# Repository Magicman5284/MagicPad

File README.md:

Welcome to the MagicPad!

This is my attempt to create a smarthome control device. 
Recently I've made a couple smart devices controlled by esp32s, so I wanted to make a device that could control them. 
The two devices it's set up to control right now are my coffee maker and my alarm clock. 
Because these are both custom projects, I don't see the MagicPad's current firmware being useful to anyone else, but that hardware can be used to control any device that can be controlled over wifi!
Because of how versatile the hardware is, it has plenty of room for future expansion such as adding games!

Assembly:
- Pretty self-explanatory for the most part, just solder the components where they are in the 3d model. 
- The one tricky part is the battery.
- To connect the battery, solder the negative wire from the battery holder into the hole in the board to the right of the buttons. 
- After this, directly solder the positive wire to the positive pin on the battery connector of the ESP32. 
- To determine which one a the positive pin, a multimeter on beeper mode can be used between both pins and ground. if it beeps, that pin is negative. 
- You also might need some additional dupont connectors to raise the screen up so it's not swallowed by the case

  Useage:
- I think the UI is pretty self-explanatory and probably no one else is ever gonna use it, so I'm not gonna bother explaining it. 
- The switch in the bottom right is a power switch
- I know this is bad design, but the device needs to be powered ON in order for it to charge. 
- Bottom left button is a back button and top right is a home button. 
- You need to input wifi and IP information in the sketch before you upload it

BOM:
| Item                                                                                                                 | Qty | Supplier            | Cost/item | Total Cost | link                                                                                                                                                                                                                                                                                                                                                                                                                                                                                                                                                                                                                                                                                                                                                                                  |
|----------------------------------------------------------------------------------------------------------------------|-----|---------------------|-----------|------------|---------------------------------------------------------------------------------------------------------------------------------------------------------------------------------------------------------------------------------------------------------------------------------------------------------------------------------------------------------------------------------------------------------------------------------------------------------------------------------------------------------------------------------------------------------------------------------------------------------------------------------------------------------------------------------------------------------------------------------------------------------------------------------------|
| 2.4 in tft screen                                                                                                    | 1   | Aliexpress          | $3.85     | $3.85      | https://www.aliexpress.us/item/3256808368541153.html?spm=a2g0o.productlist.main.3.149d3f62npL2uj&algo_pvid=60c42d40-368a-4445-8d6c-448ea058a9be&algo_exp_id=60c42d40-368a-4445-8d6c-448ea058a9be-2&pdp_ext_f=%7B%22order%22%3A%222129%22%2C%22eval%22%3A%221%22%2C%22fromPage%22%3A%22search%22%7D&pdp_npi=6%40dis%21USD%214.51%213.85%21%21%214.51%213.85%21%402103117b17940812731455001e0f3a%2112000056541994976%21sea%21US%212783459362%21X%211%210%21n_tag%3A-29919%3Bd%3Abaf43391%3Bm03_new_user%3A-29895%3BpisId%3A5000000220844609&curPageLogUid=2lMKeavTadMR&utparam-url=scene%3Asearch%7Cquery_from%3A%7Cx_object_id%3A1005008554855905%7C_p_origin_prod%3A                                                                                                                  |
| ESP32-S Development Board 2.4G Wifi Module with Battery Interface Original Ai ESP32-S for DIY IoT CH340X IP5306 Type | 1   | Aliexpress          | $6.32     | $6.32      | https://www.aliexpress.us/item/3256808312600406.html?spm=a2g0o.cart.0.0.77df38daxh0mED&mp=1&pdp_npi=6%40dis%21USD%21USD+6.97%21USD+6.32%21%21USD+6.19%21%21%21%402101e80f17940814752793414e0d72%2112000045422070092%21ct%21US%212783459362%21%211%210%21&_gl=1*10hfm7j*_gcl_aw*R0NMLjE3OTM4MjY5OTQuQ2p3S0NBaUF6S3ZYQmhCQUVpd0FCTGw5QXJHaTJzQVl2NlFzaE5UUmw4dkxZT2tkWXU5MnhxZTFSRC13d19LSW5sd281dHJEaFExc014b0NuWGNRQXZEX0J3RQ..*_gcl_dc*R0NMLjE3OTI4OTA3OTYuQ2owS0NRandydkhXQmhES0FSSXNBQm1wN2gzWWRremlEblp6RmlpOFV6R3JzMWxXNWw0WDhubmFnbzd2bUhkMEdZZW5pTHQ3bzlqbklQSWFBalZoRUFMd193Y0I.*_gcl_au*MzM2NDgyMzA5LjE3ODk1ODM4Mzc.*_ga*ODUyMzUwNzk1LjE3OTMxMzg2Mjc.*_ga_VED1YSGNC7*czE3OTQwODEyNjEkbzE4JGcxJHQxNzk0MDgxNDczJGo2JGwwJGgw&gatewayAdapt=glo2usa                               |
| 18650 battery holder                                                                                                 | 1   | Aliexpress          | $0.99     | $0.99      | https://www.aliexpress.us/item/2251832638846318.html?spm=a2g0o.cart.0.0.235338daUdxJp9&mp=1&pdp_npi=6%40dis%21USD%21USD+1.13%21USD+0.99%21%21USD+0.98%21%21%21%40210327ef17940815433297406e0d19%2164904655701%21ct%21US%212783459362%21%211%210%21&gatewayAdapt=glo2usa                                                                                                                                                                                                                                                                                                                                                                                                                                                                                                               |
| 18650 battery                                                                                                        | 1   | 18650 battery store | $4.99     | $4.99      | https://www.18650batterystore.com/products/samsung-25r-18650?variant=37119890063511&country=US&currency=USD&utm_medium=product_sync&utm_source=google&utm_content=sag_organic&utm_campaign=sag_organic&utm_campaign=23969421789&utm_source=g_c&utm_medium=cpc&utm_content=814166832664&utm_term=_&adgroupid=200718758591&gad_source=4&gad_campaignid=23969421789&gbraid=0AAAAADl22IP-T0yCTHMd2LJW7-kmlS5L0&gclid=CjwKCAiAtbvXBhB_EiwAjwv9Ji52yHABlerJVfGG0AsgF0rU-j0VmBES08tR3X1S4KTzMIlJhsAiJhoC3NIQAvD_BwE                                                                                                                                                                                                                                                                          |
| minitoggle switch 3 prongs                                                                                           | 1   | Aliexpress          | $3.82     | $3.82      | https://www.aliexpress.us/item/3256808118023831.html?spm=a2g0o.productlist.main.4.339f31cfuvqRyR&aem_p4p_detail=202611071200442267456020120960004589159&algo_pvid=ffc93556-7054-4d00-a989-105471204cdd&algo_exp_id=ffc93556-7054-4d00-a989-105471204cdd-3&pdp_ext_f=%7B%22order%22%3A%223770%22%2C%22eval%22%3A%221%22%2C%22fromPage%22%3A%22search%22%7D&pdp_npi=6%40dis%21USD%214.54%213.82%21%21%2130.10%2125.31%21%4021030cd817940816442355963e0f71%2112000044555585169%21sea%21US%212783459362%21X%211%210%21n_tag%3A-29919%3Bd%3Abaf43391%3Bm03_new_user%3A-29895%3BpisId%3A5000000220844609&curPageLogUid=bxfWoncg7wrM&utparam-url=scene%3Asearch%7Cquery_from%3A%7Cx_object_id%3A1005008304338583%7C_p_origin_prod%3A&search_p4p_id=202611071200442267456020120960004589159_1 |
| EC11 rotary encoder with push button                                                                                 | 1   | Aliexpress          | $1.37     | $1.37      | https://www.aliexpress.us/item/3256807457768762.html?spm=a2g0o.productlist.main.3.5e1068b6ZSGLHV&algo_pvid=103bbf53-d7ff-41ed-948a-e11e77e458db&algo_exp_id=103bbf53-d7ff-41ed-948a-e11e77e458db-2&pdp_ext_f=%7B%22order%22%3A%224956%22%2C%22eval%22%3A%221%22%2C%22fromPage%22%3A%22search%22%7D&pdp_npi=6%40dis%21USD%211.52%211.32%21%21%211.52%211.32%21%4021030f4a17940817013391423e0ff3%2112000041630839409%21sea%21US%212783459362%21X%211%210%21n_tag%3A-29919%3Bd%3Abaf43391%3Bm03_new_user%3A-29895%3BpisId%3A5000000220844609&curPageLogUid=uPza42i6Mwl9&utparam-url=scene%3Asearch%7Cquery_from%3A%7Cx_object_id%3A1005007644083514%7C_p_origin_prod%3A                                                                                                                  |
| 10k resistor                                                                                                         | 1   | Aliexpress          | $1.53     | $1.53      | https://www.aliexpress.us/item/3256809143779506.html?spm=a2g0o.productlist.main.3.5a782a0a1rcJxt&algo_pvid=45ee8b2b-bcd2-4eb7-80b8-ee1bf72b4ad2&algo_exp_id=45ee8b2b-bcd2-4eb7-80b8-ee1bf72b4ad2-2&pdp_ext_f=%7B%22order%22%3A%229099%22%2C%22eval%22%3A%221%22%2C%22fromPage%22%3A%22search%22%7D&pdp_npi=6%40dis%21USD%211.81%211.53%21%21%2111.99%2110.12%21%402101e80f17940817994392860e1068%2112000048778024089%21sea%21US%212783459362%21X%211%210%21n_tag%3A-29919%3Bd%3Abaf43391%3Bm03_new_user%3A-29895%3BpisId%3A5000000220405735&curPageLogUid=K5N1yOKL6CDi&utparam-url=scene%3Asearch%7Cquery_from%3A%7Cx_object_id%3A1005009330094258%7C_p_origin_prod%3A                                                                                                                |
| 1x10 dupont connectors                                                                                               | 1   | Aliexpress          | $2.83     | $2.83      | https://www.aliexpress.us/item/3256811876826434.html?spm=a2g0o.cart.0.0.568d38danzfLHR&mp=1&pdp_npi=6%40dis%21USD%21USD+2.85%21USD+2.37%21%21USD+2.37%21%21%21%402101e80f17940820156671223e0d72%2112000057466932458%21ct%21US%212783459362%21%211%210%21&_gl=1*ruz3ms*_gcl_aw*R0NMLjE3OTM4MjY5OTQuQ2p3S0NBaUF6S3ZYQmhCQUVpd0FCTGw5QXJHaTJzQVl2NlFzaE5UUmw4dkxZT2tkWXU5MnhxZTFSRC13d19LSW5sd281dHJEaFExc014b0NuWGNRQXZEX0J3RQ..*_gcl_dc*R0NMLjE3OTI4OTA3OTYuQ2owS0NRandydkhXQmhES0FSSXNBQm1wN2gzWWRremlEblp6RmlpOFV6R3JzMWxXNWw0WDhubmFnbzd2bUhkMEdZZW5pTHQ3bzlqbklQSWFBalZoRUFMd193Y0I.*_gcl_au*MzM2NDgyMzA5LjE3ODk1ODM4Mzc.*_ga*ODUyMzUwNzk1LjE3OTMxMzg2Mjc.*_ga_VED1YSGNC7*czE3OTQwODEyNjEkbzE4JGcxJHQxNzk0MDgyMDE4JGoyNCRsMCRoMA..&gatewayAdapt=glo2usa                            |
| 1x4 dupont connectors                                                                                                | 1   | Aliexpress          | $2.37     | $2.37      | https://www.aliexpress.us/item/3256811876826434.html?spm=a2g0o.cart.0.0.568d38danzfLHR&mp=1&pdp_npi=6%40dis%21USD%21USD+2.85%21USD+2.37%21%21USD+2.37%21%21%21%402101e80f17940820156671223e0d72%2112000057466932458%21ct%21US%212783459362%21%211%210%21&_gl=1*ruz3ms*_gcl_aw*R0NMLjE3OTM4MjY5OTQuQ2p3S0NBaUF6S3ZYQmhCQUVpd0FCTGw5QXJHaTJzQVl2NlFzaE5UUmw4dkxZT2tkWXU5MnhxZTFSRC13d19LSW5sd281dHJEaFExc014b0NuWGNRQXZEX0J3RQ..*_gcl_dc*R0NMLjE3OTI4OTA3OTYuQ2owS0NRandydkhXQmhES0FSSXNBQm1wN2gzWWRremlEblp6RmlpOFV6R3JzMWxXNWw0WDhubmFnbzd2bUhkMEdZZW5pTHQ3bzlqbklQSWFBalZoRUFMd193Y0I.*_gcl_au*MzM2NDgyMzA5LjE3ODk1ODM4Mzc.*_ga*ODUyMzUwNzk1LjE3OTMxMzg2Mjc.*_ga_VED1YSGNC7*czE3OTQwODEyNjEkbzE4JGcxJHQxNzk0MDgyMDE4JGoyNCRsMCRoMA..&gatewayAdapt=glo2usa                            |
| Cherry mx swicthes                                                                                                   | 1   | Aliexpress          | $3.69     | $3.69      | https://www.aliexpress.us/item/3256812387735845.html?spm=a2g0o.productlist.main.3.48c53bb7ccRP0Z&algo_pvid=d6bec1c6-d25e-4a9b-a5d0-892486b8272f&algo_exp_id=d6bec1c6-d25e-4a9b-a5d0-892486b8272f-2&pdp_ext_f=%7B%22order%22%3A%229%22%2C%22eval%22%3A%221%22%2C%22fromPage%22%3A%22search%22%7D&pdp_npi=6%40dis%21USD%217.38%213.69%21%21%2148.94%2124.47%21%402101ef5e17940822322147882e0dff%2112000058752996423%21sea%21US%212783459362%21X%211%210%21n_tag%3A-29919%3Bd%3Abaf43391%3Bm03_new_user%3A-29895&curPageLogUid=uhg1IY7N6ELF&utparam-url=scene%3Asearch%7Cquery_from%3A%7Cx_object_id%3A1005012574050597%7C_p_origin_prod%3A                                                                                                                                              |
| keycaps                                                                                                              | 1   | Aliexpress          | $2.02     | $2.02      | https://www.aliexpress.us/item/3256813177462628.html?spm=a2g0o.productlist.main.17.7de0737ao0EwwI&algo_pvid=5b236d3c-d623-44a7-9012-2891db2fc2b6&algo_exp_id=5b236d3c-d623-44a7-9012-2891db2fc2b6-16&pdp_ext_f=%7B%22order%22%3A%221%22%2C%22eval%22%3A%221%22%2C%22fromPage%22%3A%22search%22%7D&pdp_npi=6%40dis%21USD%213.93%211.63%21%21%2126.06%2110.80%21%402101e75417940823470156864e0df9%2112000060986788015%21sea%21US%212783459362%21X%211%210%21n_tag%3A-29919%3Bd%3Abaf43391%3Bm03_new_user%3A-29895%3BpisId%3A5000000220906888&curPageLogUid=Vra1xloKuPlE&utparam-url=scene%3Asearch%7Cquery_from%3A%7Cx_object_id%3A1005013363777380%7C_p_origin_prod%3A                                                                                                                 |
| PCB                                                                                                                  | 1   | JLCPCB              | $20.08    | $20.08     | https://jlcpcb.com/                                                                                                                                                                                                                                                                                                                                                                                                                                                                                                                                                                                                                                                                                                                                                                   |
| Estimated total shipping                                                                                             | 1   |                     |           | $0.00      |                                                                                                                                                                                                                                                                                                                                                                                                                                                                                                                                                                                                                                                                                                                                                                                       |

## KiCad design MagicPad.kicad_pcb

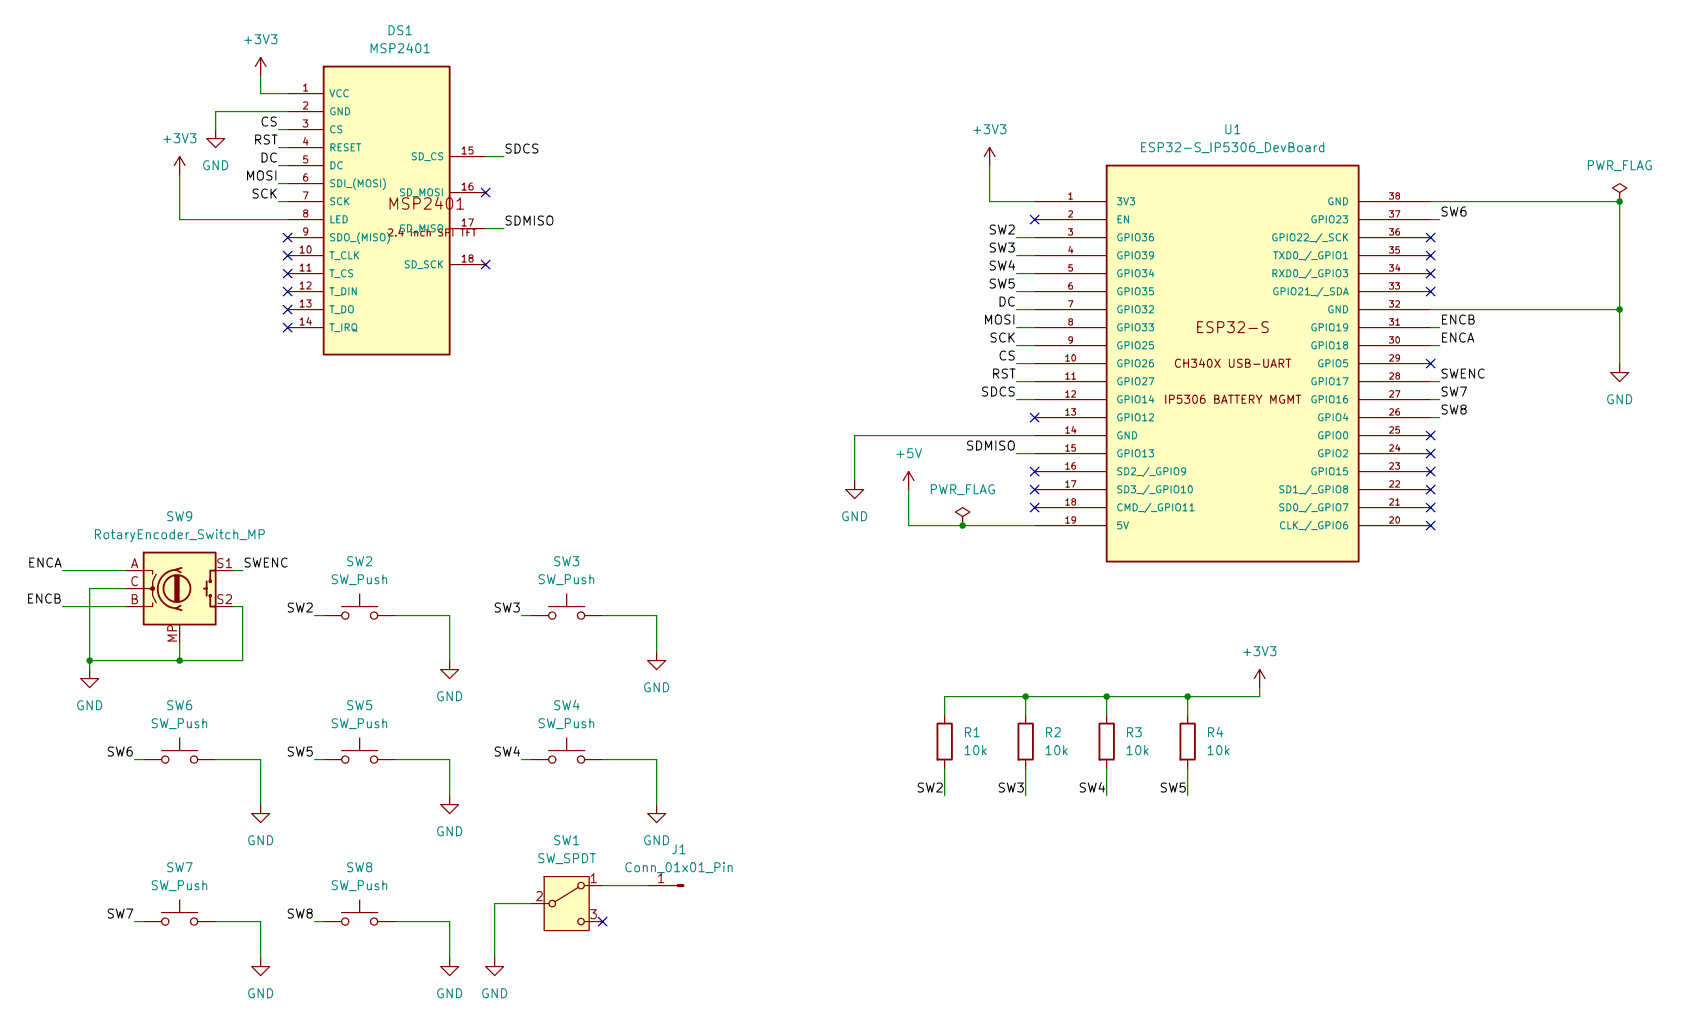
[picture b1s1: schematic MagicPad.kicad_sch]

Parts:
DS1: MSP2401
J1: Conn_01x01_Pin; PinHeader_1x01_P2.54mm_Vertical
R1, R2, R3, R4: 10k; R_Axial_DIN0204_L3.6mm_D1.6mm_P7.62mm_Horizontal
SW1: SW_SPDT; MiniToggle_SPDT_3Lug
SW2, SW3, SW4, SW5, SW6, SW7, SW8: SW_Push; SW_Cherry_MX_1.00u_PCB
SW9: RotaryEncoder_Switch_MP; RotaryEncoder_Alps_EC11E-Switch_Vertical_H20mm
U1: ESP32-S_IP5306_DevBoard; ESP32S_IP5306

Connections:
+3V3: DS1.1 (VCC), DS1.8 (LED), R1.1, R2.1, R3.1, R4.1, U1.1 (3V3)
+5V: U1.19 (5V)
/CS: DS1.3 (CS), U1.10 (GPIO26)
/DC: DS1.5 (DC), U1.7 (GPIO32)
/ENCA: SW9.A, U1.30 (GPIO18)
/ENCB: SW9.B, U1.31 (GPIO19)
/MOSI: DS1.6 (SDI_(MOSI)), U1.8 (GPIO33)
/RST: DS1.4 (RESET), U1.11 (GPIO27)
/SCK: DS1.7 (SCK), U1.9 (GPIO25)
/SDCS: DS1.15 (SD_CS), U1.12 (GPIO14)
/SDMISO: DS1.17 (SD_MISO), U1.15 (GPIO13)
/SW2: R1.2, SW2.1, U1.3 (GPIO36)
/SW3: R2.2, SW3.1, U1.4 (GPIO39)
/SW4: R3.2, SW4.1, U1.5 (GPIO34)
/SW5: R4.2, SW5.1, U1.6 (GPIO35)
/SW6: SW6.1, U1.37 (GPIO23)
/SW7: SW7.1, U1.27 (GPIO16)
/SW8: SW8.1, U1.26 (GPIO4)
/SWENC: SW9.S1, U1.28 (GPIO17)
GND: DS1.2 (GND), SW1.2 (B), SW2.2, SW3.2, SW4.2, SW5.2, SW6.2, SW7.2, SW8.2, SW9.C, SW9.MP, SW9.S2, U1.14 (GND), U1.32 (GND), U1.38 (GND)
unnamed: J1.1 (Pin_1_1), SW1.1 (A)

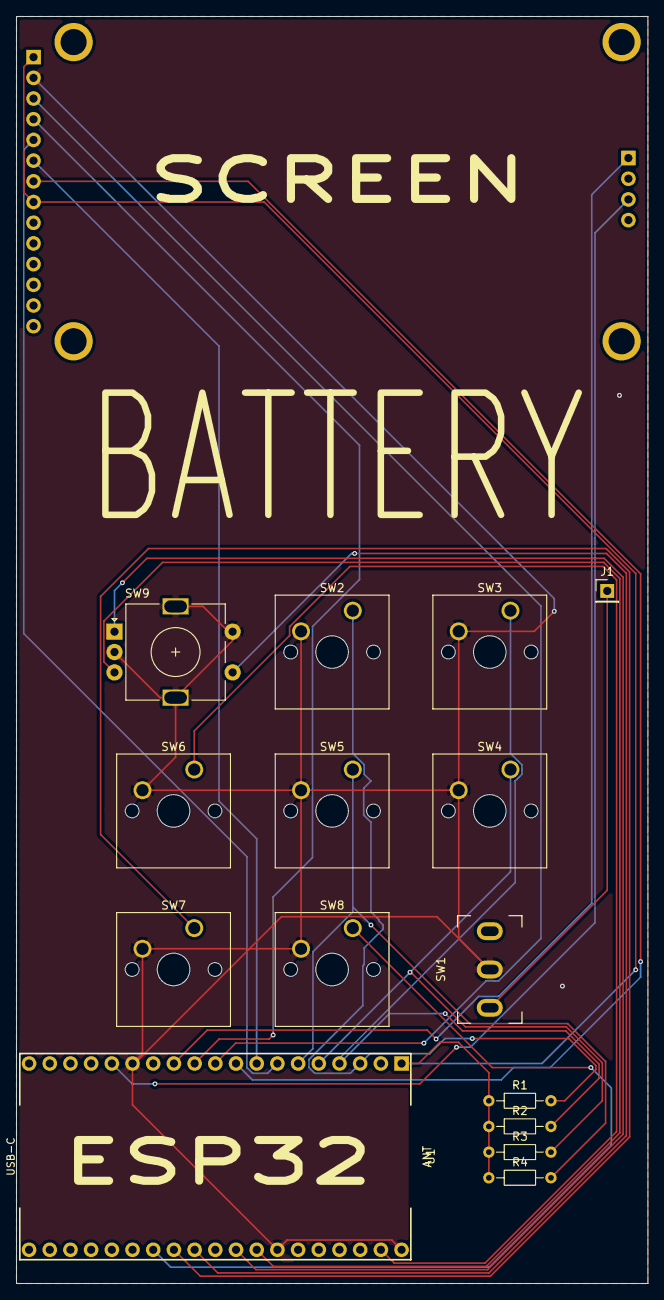
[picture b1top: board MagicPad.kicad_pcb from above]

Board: 2 copper layers, 77.5 x 155.5 mm, 16 parts (0 on the bottom side), 20 nets.
